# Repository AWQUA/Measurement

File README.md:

# Measurement
 This repo fully details all of AWQUA's tools for measuring water quality, with each water quality parameter in a separate subdirectory. The performance standards for these devices, and their suggested use in a water quality monitoring program, will be detailed in [Standards](https://github.com/AWQUA/Standards), and methods for communicating the data obtained through these water quality measurement tools will be described in [Communication](https://github.com/AWQUA/Communication).

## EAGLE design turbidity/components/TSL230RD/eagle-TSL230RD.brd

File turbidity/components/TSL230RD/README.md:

##AWQUA Testing documentation: TSL230RD
####**tags: turbidity, TSL230RD, light-to-frequency sensors**

##1. Component selection
Selected for turbidity detection. Mentioned in several blog posts and in two patent applications as a potentially suitable sensor for turbidity detection. Sensitive to very hight and low light levels.  
_Completed: 2014 (documentation completed 2015-07-14)_
##2. Breakout board design
**Design logic:**  
Voltage: 2.7-5.5V  
Bypass capacitor value: 100nF  
One Frequency output pin,  two sensitivity selection pins, two frequency scaling pins; output-enable pin  
[Datasheet](datasheet-TSL230RD.pdf)  
[Pinout](pinout-TSL230RD.jpg)  
[Suggested footprint](suggested-footprint-TSL230RD.jpg)  
[Eagle schematic](eagle-schematic-TSL230RD.jpg)  
[Eagle board](eagle-board-TSL230RD.jpg)  
[Test board](test-board-TSL230RD.jpg)  
[Solder mask] (solder-mask-TSL230RD.pdf)  
_Completed: 2015-07-14 (partially completed in 2014)_
##3. Board fabrication  
Check back soon -- this board is being manufactured by [OSHPark](http://oshpark.com) _as you read this_!
##4. Testing
(This component has been tested as part of a low-cost turbidimeter. For test results, see the AWQUA [`basic handheld turbidimeter`](https://github.com/AWQUA/Measurement/tree/master/turbidity/basic-handheld-turbidimeter)    
##5. Development of monitoring device  
This component has been used in an AWQUA device. Check out the [`basic handheld turbidimeter`](https://github.com/AWQUA/Measurement/tree/master/turbidity/basic-handheld-turbidimeter)!

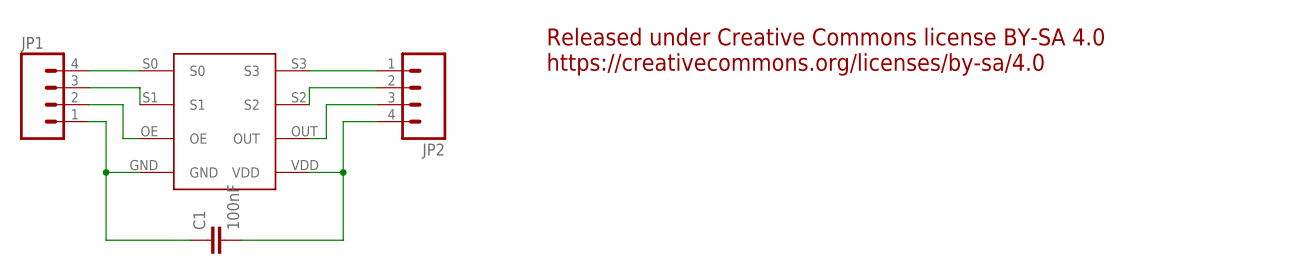
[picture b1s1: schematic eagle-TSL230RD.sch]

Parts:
C1: 100nF; 0805
JP1, JP2: M04PTH; 1X04
U$1: TSL230RDSMD; TSL230RD

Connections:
unnamed: JP1.4, U$1.S0
unnamed: JP1.3, U$1.S1
unnamed: JP1.2, U$1.OE
unnamed: C1.1, JP1.1, U$1.GND
unnamed: JP2.1, U$1.S3
unnamed: JP2.2, U$1.S2
unnamed: JP2.3, U$1.OUT
unnamed: C1.2, JP2.4, U$1.VDD

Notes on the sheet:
Released under Creative Commons license BY-SA 4.0 https://creativecommons.org/licenses/by-sa/4.0

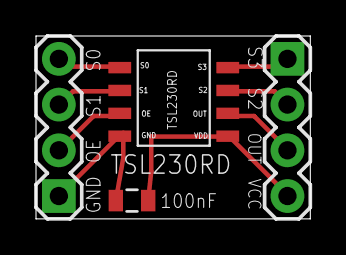
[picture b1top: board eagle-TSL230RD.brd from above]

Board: 2 copper layers, 15.2 x 10.2 mm, 4 parts (0 on the bottom side), 8 nets.

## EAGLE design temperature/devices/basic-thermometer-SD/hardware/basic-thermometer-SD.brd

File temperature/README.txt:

Contribute your designs to AWQUA! Help make water quality monitoring affordable for all citizens of Earth.

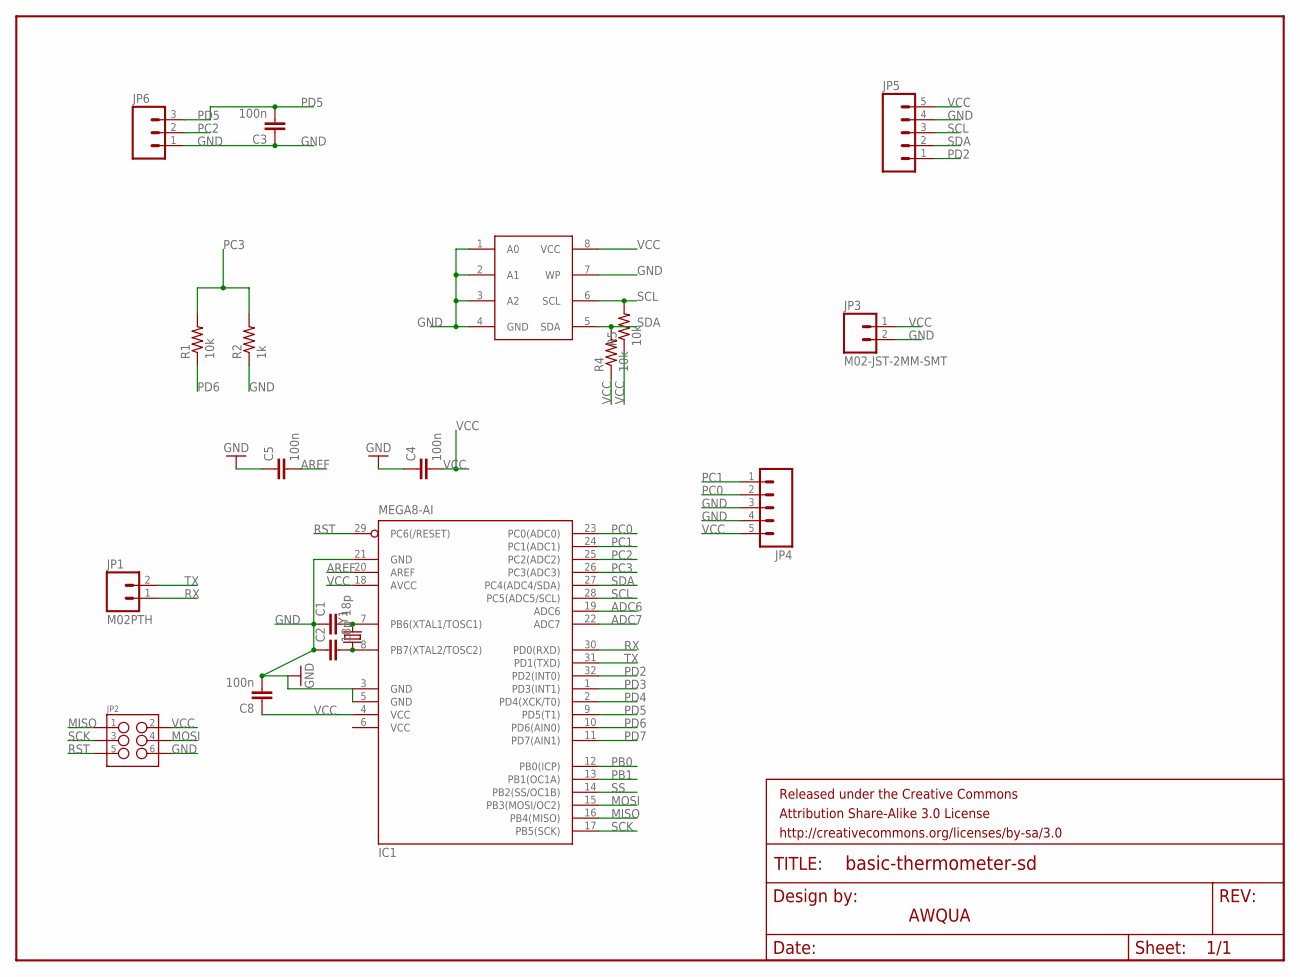
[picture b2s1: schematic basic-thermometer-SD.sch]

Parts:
C1, C2: 18p; 0603-CAP
C3, C4, C5, C8: 100n; 0603-CAP
EEPROM: AT24C256; SOIC8-LONGPAD
FRAME1: FRAME-LETTER; CREATIVE_COMMONS
IC1: MEGA8-AI; TQFP32-08
JP1: M02PTH; 1X02
JP2: M03X22X3_SILK_SM; 2X3
JP3: M02-JST-2MM-SMT; JST-2-SMD
JP4, JP5: M05PTH; 1X05
JP6: M03PTH; 1X03
R1, R4, R5: 10k; 0603-RES
R2: 1k; 0603-RES
Y1: CRYSTAL5X3; CRYSTAL-SMD-5X3

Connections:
ADC6: IC1.19 (ADC6)
ADC7: IC1.22 (ADC7)
AREF: C5.2, IC1.20 (AREF)
GND: C1.1, C2.1, C3.1, C4.1, C5.1, C8.2, EEPROM.1 (A0), EEPROM.2 (A1), EEPROM.3 (A2), EEPROM.4 (GND), EEPROM.7 (WP), IC1.3 (GND), IC1.5 (GND), IC1.21 (GND), JP2.6, JP3.2 (1), JP4.3, JP4.4, JP5.4, JP6.1, R2.1
MISO: IC1.16 (PB4(MISO)), JP2.1
MOSI: IC1.15 (PB3(MOSI/OC2)), JP2.4
PB0: IC1.12 (PB0(ICP))
PB1: IC1.13 (PB1(OC1A))
PC0: IC1.23 (PC0(ADC0)), JP4.2
PC1: IC1.24 (PC1(ADC1)), JP4.1
PC2: IC1.25 (PC2(ADC2)), JP6.2
PC3: IC1.26 (PC3(ADC3)), R1.2, R2.2
PD2: IC1.32 (PD2(INT0)), JP5.1
PD3: IC1.1 (PD3(INT1))
PD4: IC1.2 (PD4(XCK/T0))
PD5: C3.2, IC1.9 (PD5(T1)), JP6.3
PD6: IC1.10 (PD6(AIN0)), R1.1
PD7: IC1.11 (PD7(AIN1))
Q1: C2.2, IC1.8 (PB7(XTAL2/TOSC2)), Y1.1
Q2: C1.2, IC1.7 (PB6(XTAL1/TOSC1)), Y1.3 (2)
RST: IC1.29 (PC6(/RESET)), JP2.5
RX: IC1.30 (PD0(RXD)), JP1.1
SCK: IC1.17 (PB5(SCK)), JP2.3
SCL: EEPROM.6 (SCL), IC1.28 (PC5(ADC5/SCL)), JP5.3, R5.2
SDA: EEPROM.5 (SDA), IC1.27 (PC4(ADC4/SDA)), JP5.2, R4.2
SS: IC1.14 (PB2(SS/OC1B))
TX: IC1.31 (PD1(TXD)), JP1.2
VCC: C4.2, C8.1, EEPROM.8 (VCC), IC1.4 (VCC), IC1.6 (VCC), IC1.18 (AVCC), JP2.2, JP3.1 (2), JP4.5, JP5.5, R4.1, R5.1

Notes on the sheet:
AWQUA

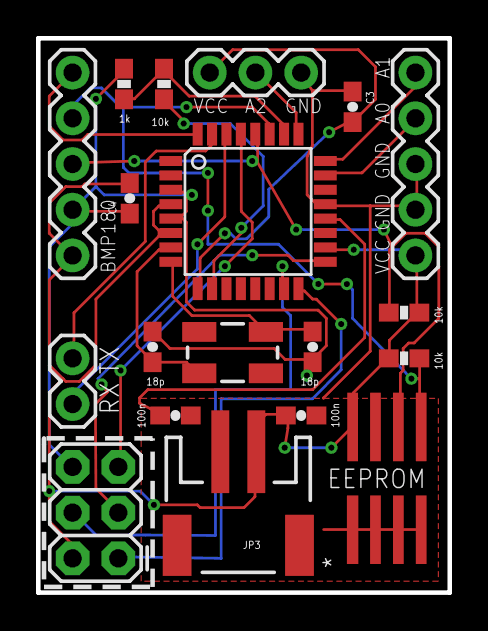
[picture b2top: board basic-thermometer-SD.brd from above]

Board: 2 copper layers, 22.9 x 30.8 mm, 21 parts (1 on the bottom side), 20 nets.

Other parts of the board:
U$1: OSHW-LOGO-S

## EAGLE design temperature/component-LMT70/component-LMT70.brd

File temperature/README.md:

# Measuring Temperature
##Why
Temperature is an important variable in the treatment of drinking water. While cheap commercial thermometers are already widely available, we aim to provide a range of thermometers that can be easily modified, outfitted with additional sensors, and paired with communications modules for telemetry of data.

##How
We have a range of tested thermometer designs. Current models are listed below, with attribute tags next to their links. Here is a quick explanation of those attribute tags:

[H] Handheld -- device is manually operated and portable  
[D] Desktop -- device is intended for stationary operation  
[B] Battery powered  
[A] Automated  
[WR] Water Resistant -- can be splashed without damaging internal electronics, but _not_ waterproof  
[I_n] Immersible -- waterproof and can withstand immersion to n meters  

* [H][B][`basic-thermometer`](basic-thermometer/) Our most basic model, which can timestamp and store 8000 temperature observations.

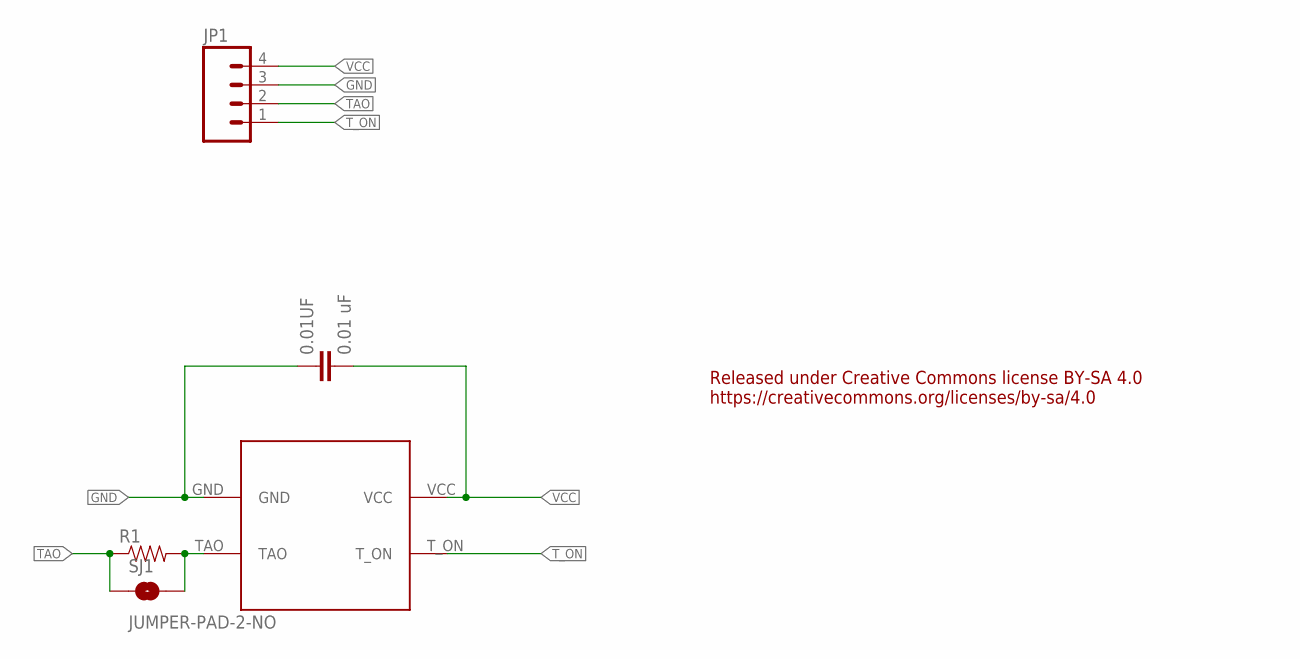
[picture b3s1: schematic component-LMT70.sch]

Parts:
0.01UF: 0.01 uF; 0603-CAP
JP1: M04NO_SILK_ALL_ROUND; 1X04_NO_SILK_ALL_ROUND
R1: RESISTOR0603-RES; 0603-RES
SJ1: JUMPER-PAD-2-NO; PAD-JUMPER-2-NO_NO_SILK
U$1: LMT70; LMT-70

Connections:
GND: 0.01UF.1, JP1.3, U$1.GND
unnamed: R1.2, SJ1.2, U$1.TAO
TAO: JP1.2, R1.1, SJ1.1
T_ON: JP1.1, U$1.T_ON
VCC: 0.01UF.2, JP1.4, U$1.VCC

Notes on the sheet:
Released under Creative Commons license BY-SA 4.0 https://creativecommons.org/licenses/by-sa/4.0

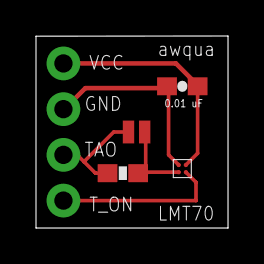
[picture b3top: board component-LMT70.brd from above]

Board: 2 copper layers, 10.7 x 10.7 mm, 5 parts (0 on the bottom side), 5 nets.

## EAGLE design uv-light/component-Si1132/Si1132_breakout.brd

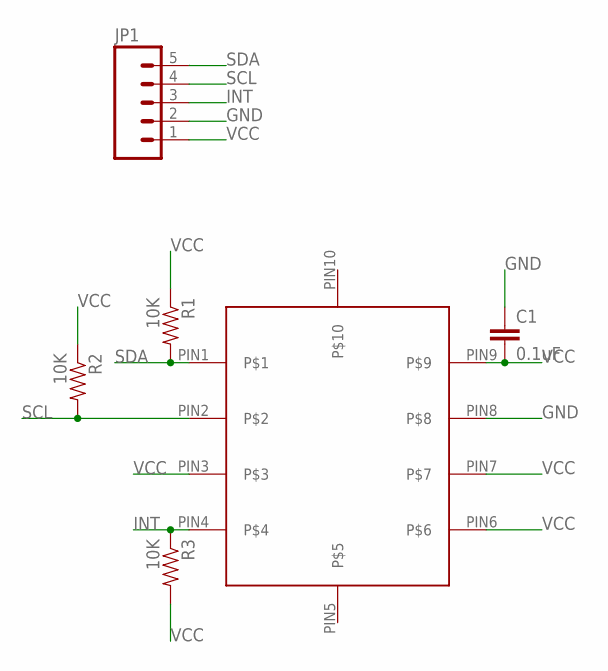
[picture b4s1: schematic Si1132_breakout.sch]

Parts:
C1: 0.1uF; 0603-CAP
JP1: M05PTH; 1X05
R1, R2, R3: 10K; 0603-RES
U$1: SI1132

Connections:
GND: C1.1, JP1.2, U$1.PIN8
INT: JP1.3, R3.1, U$1.PIN4
SCL: JP1.4, R2.2, U$1.PIN2
SDA: JP1.5, R1.2, U$1.PIN1
VCC: C1.2, JP1.1, R1.1, R2.1, R3.2, U$1.PIN3, U$1.PIN6, U$1.PIN7, U$1.PIN9

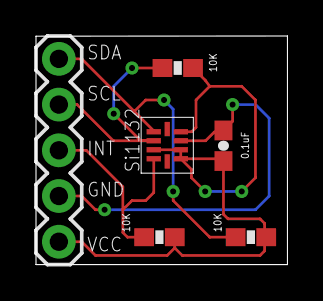
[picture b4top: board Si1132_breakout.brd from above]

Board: 2 copper layers, 14.0 x 12.7 mm, 6 parts (0 on the bottom side), 5 nets.

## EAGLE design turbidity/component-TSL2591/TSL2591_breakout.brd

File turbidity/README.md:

# Measuring Turbidity

##Why
Turbidity refers to the dirtiness or cloudiness of a water sample. Typically the majority of cloudiness in a water sample is due to suspended sediments, which can harbor pathogens and hamper the effectiveness of chemical and optical disinfection methods. Thus, while turbidity is not itself harmful, it serves as a simple real-time proxy measurement for water quality. Technicians at water treatment plants regularly measure water turbidity before and after treatment. It’s a legal requirement in many countries, and one indicator of whether treated water is safe for human consumption.

The unaided eye can distinguish cloudy water from clear water, but even visibly clear samples of water can have dangerous levels of turbidity. The standard tool for measuring turbidity (a turbidimeter) is a complex piece of equipment. Handheld units capable of analyzing a single sample vial cost several hundred dollars; automated units capable of intermittently analyzing samples from a column of flowing water can cost several thousand. An affordable, open-source solution for turbidity sampling would be a major step towards assuring the quality and sustainability of programs that seek to expand global access to treated drinking water.

##How
We have a range of tested turbidimeter designs, from barebones handheld devices to automated inline devices with dynamically updatable operating parameters and long-range data telemetry. Please note, any project name that begins with 'component' (such as ['component-TSL230RD']) is an evaluation of a sensor, not a full-fledged monitoring device.

Current models are listed below, with attribute tags next to their links. Here is a quick explanation of those attribute tags:

[H] Handheld -- device is manually operated and portable  
[D] Desktop -- device is intended for stationary operation  
[B] Battery powered  
[A] Automated  
[WR] Water Resistant -- can be splashed without damaging internal electronics, but _not_ waterproof  
[I] Immersible -- waterproof and can withstand immersion to at least one meter  

* [H][B][`basic-handheld-turbidimeter`](devices/basic-handheld-turbidimeter/) A simple, effective, lowest-cost device for manual turbidity measurments.

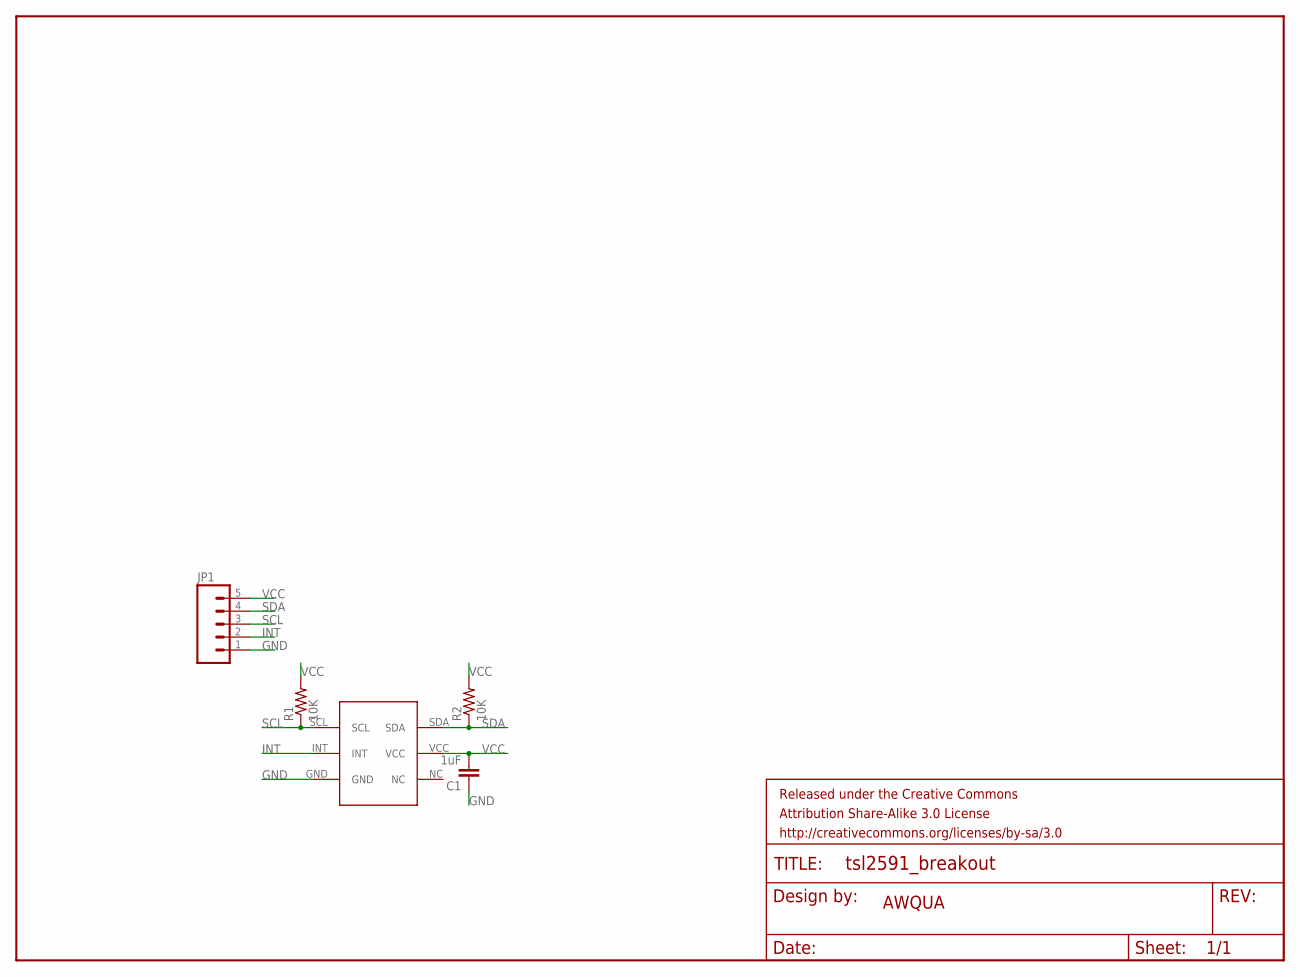
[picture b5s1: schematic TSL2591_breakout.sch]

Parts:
C1: 1uF; 0603-CAP
FRAME1: FRAME-LETTER; CREATIVE_COMMONS
JP1: M05NO_SILK; 1X05_NO_SILK
R1, R2: 10K; 0603-RES
U$1: TSL2591

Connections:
GND: C1.1, JP1.1, U$1.GND
INT: JP1.2, U$1.INT
SCL: JP1.3, R1.1, U$1.SCL
SDA: JP1.4, R2.1, U$1.SDA
VCC: C1.2, JP1.5, R1.2, R2.2, U$1.VCC

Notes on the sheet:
AWQUA

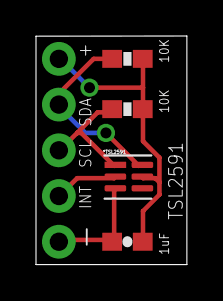
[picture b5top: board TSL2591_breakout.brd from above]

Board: 2 copper layers, 8.4 x 12.7 mm, 6 parts (0 on the bottom side), 5 nets.

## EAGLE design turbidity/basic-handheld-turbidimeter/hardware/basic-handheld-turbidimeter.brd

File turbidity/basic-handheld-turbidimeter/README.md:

#Basic Handheld Turbidimeter
##Purpose  
The Basic Handheld Turbidimeter is designed to measure turbidity on demand, portably, for the lowest possible price.  

##Function  
_How does the device measure a parameter?_  
This device is a single-beam [nephelometrer](https://en.wikipedia.org/wiki/Nephelometer). Light from an infrared light-emitting diode (IR LED) is scattered by suspended sediment as it passes through a sample of water. This scattered light is detected by an IR-sensitive [photodiode](https://en.wikipedia.org/wiki/Photodiode) mounted at a right angle to the center of the IR LED's light beam. The intensity of light detected by the photodiode is referenced to a calibration curve stored in the device's memory to interpolate the corresponding turbidity value, measured in [nephelometric turbidity units (NTU)](http://or.water.usgs.gov/grapher/fnu.html).  

_How does the device record data?_  
This device is intended for basic manual operation and does not contain storage for data.   

_How does the device display data?_  
The microcontroller at the heart of this device reads the frequency of pulses transmitted by the [photodiode unit](http://www.mouser.com/ProductDetail/ams/TSL230BRD-TR/?qs=sGAEpiMZZMu97qiQi8P%252buifvOPr%252b402N67DKHn09PFo%3d), interpolates the turbidity value from stored calibration data, and displays the turbidity value on a [four-digit display panel](http://www.electrodragon.com/product/7-segment-4-digit-display-common-anode/) (much like those used in some alarm clocks).

_What units does the device report in?_  
Like all AWQUA turbidimeters, this device reports readings in  [nephelometric turbidity units (NTU)](http://or.water.usgs.gov/grapher/fnu.html).  

_How does the device communicate data electronically?_  
This device does not possess data telemetry capabilities.  

##Use Case  
_Where can the device be safely used?_  
This device can handle temperatures up to 70C, and is intended for field conditions. It is not water proof or water resistent, however.

##Power  
_How is the device powered?_  
This device uses 3.3V DC power, and requires less than 100mA of current. A standard 3.7V lithium ion or polymer battery, or three AA alkaline batteries, would suffice to power it.

_How much power does it use?_  
In semi-automated testing, this device was capable of taking 5000 measurements on one set of three AA batteries.

##Standard and Testing  
_How was the device tested?_  
Testing procedures for this device are described in full in [An Affordable Open-Source Turbidimeter](http://www.mdpi.com/1424-8220/14/4/7142).

_How did it perform?_  
Testing results for this device are described in full in [An Affordable Open-Source Turbidimeter](http://www.mdpi.com/1424-8220/14/4/7142). The figure below shows the performance of this model of device, versus a popular commercial turbidimeter.  

_What performance standards does the device meet?_  
This device was designed and successfully tested to reliably measure turbidity values well below 1.0 NTU, which is the maximum turbidity value recommended by the World Health Organization for drinking water prior to disinfection. Please note however that this device is not certified to meet EPA requirements for the routine turbidity monitoring of treated drinking water in the United States. 

_What monitoring standards can this device be used to meet?_  
This device is one of several proven turbidimeter designs out there that can be used to meet international and World Health Organization guidelines on turbidity monitoring, yet are not able to meet the very exacting (and expensive) American and European turbidity detection standards. There is an urgent global need for simple, affordable turbidity detection, and AWQUA members are working to establish alternative turbidity detection standards to address this need. Please check out our [Standards](https://github.com/AWQUA/Standards) repository for more information.

##Construction  

###Bill of Materials
| Quantity  | Part Description | Example Price (each) |
| :-------------: | ------------- | :-------------: |
| 1 | ATMega328P-PU microprocessor  | [$2.90](http://www.electrodragon.com/product/atmega328-with-arduino-optiboot-uno/)|
| 1 | 4-digit, 7-segment display  | [$2.10](http://www.electrodragon.com/product/7-segment-4-digit-display-common-anode/)|
| 1 | 74HC595 shift register  | [$0.62](http://www.mouser.com/ProductDetail/Texas-Instruments/SN74HC595N/?qs=sGAEpiMZZMuyBeSSR239IeaeNSzgQbS%2f1btldJdqa6k%3d) |
| 1 | LMT86 temperature sensor  | [$1.00](http://www.mouser.com/ProductDetail/Texas-Instruments/LMT86LP/?qs=sGAEpiMZZMvfFCidbTccA1jyVRrxk5nB%252bTEjPRynSGM%3d)|
| 1 | TSL230BRD  | [$5.03](http://www.mouser.com/ProductDetail/ams/TSL230BRD-TR/?qs=sGAEpiMZZMu97qiQi8P%252buifvOPr%252b402N67DKHn09PFo%3d)|
| 1 | LF33ABV 3.3V Voltage regulator  | [$1.03](http://www.mouser.com/ProductDetail/STMicroelectronics/LF33ABV/?qs=sGAEpiMZZMsGz1a6aV8DcBQiArhhid1gDswAeAw%2fIB0%3d)|
| 2 | 10uF aluminum electrolytic capacitors  | [$0.24](http://www.mouser.com/ProductDetail/Nichicon/ULD1J100MDD1TD/?qs=sGAEpiMZZMvwFf0viD3Y3c1N%2fF%2fpDmX12XlNW9X9Y3vZmYyMo5GpOw%3d%3d)|
| 2 | 22pF ceramic capacitors  | [$0.03](http://www.mouser.com/ProductDetail/Vishay-BC-Components/K220J10C0GF5UH5/?qs=sGAEpiMZZMsh%252b1woXyUXj9nJp%252b8gphztXIKBUu3gv%252bs%3d)|
| 5 | 100nF ceramic capacitors  | [$0.06](http://www.mouser.com/ProductDetail/Vishay-BC-Components/K104Z15Y5VE5TL2/?qs=sGAEpiMZZMsh%252b1woXyUXj5VNmf0jXPWIrWjnp1zAXac%3d)|
| 4 | 100 ohm resistors  | [$0.10](http://www.mouser.com/ProductDetail/KOA-Speer/MOS1-2CT52R101J/?qs=sGAEpiMZZMtlubZbdhIBICYVxaT5CDYBpEIIN%2f0BoAk%3d)|
| 1 | 220 ohm resistors  | [$0.10](http://www.mouser.com/ProductDetail/KOA-Speer/MOS1-2CT52R221J/?qs=sGAEpiMZZMtlubZbdhIBICYVxaT5CDYBStqm8FrIljg%3d)|
| 1 | 1K ohm resistors 1% tolerance | [$0.10](http://www.mouser.com/ProductDetail/Vishay-Beyschlag/MBB02070C1001FCT00/?qs=sGAEpiMZZMtlubZbdhIBIAA6NYEPHyksoxlYyK2s%252btM%3d)|
| 4 | 10K ohm resistors  | [$0.10](http://www.mouser.com/ProductDetail/Vishay-Beyschlag/MBA02040C1002FCT00/?qs=sGAEpiMZZMtlubZbdhIBIP7908E9uONJr6Tgqqo7oLA%3d)|
| 1 | IR LED  | [$0.47](http://www.mouser.com/ProductDetail/Kingbright/WP7113SF4C/?qs=sGAEpiMZZMvAL21a%2fDhxMro1KOf4QOs%252bCw5JRgjZK8o%3d)|
| 1 | LED lighting driver | [$0.43](http://www.mouser.com/Search/ProductDetail.aspx?R=AL5809-30S1-7virtualkey62110000virtualkey621-AL5809-30S1-7)|
| 1 | Momentary contact button  | [$0.91](http://www.mouser.com/ProductDetail/Mountain-Switch/104-0013-EVX/?qs=sGAEpiMZZMvxtGF7dlGNpr35VnaTB25ys95hy84%252ba4o%3d)|
| 1 | SPST power switch  | [$1.15](http://www.mouser.com/ProductDetail/CHERRY/TRG22F2FBBNN/?qs=sGAEpiMZZMtNT9UGfLL4eOd3cDQgL8vM5i2VNLX9H3E%3d)|
| 100 | Header pins (0.1" spacing)  | [$.00225](http://www.electrodragon.com/product/break-away-header/)|
|||
||**Total Cost:**|**$17.70**|
###Circuit Board
####Schematic

####Layout

###Assembly
For assembly instructions, see the [Supplementary Materials](http://www.mdpi.com/1424-8220/14/4/7142/s1) for An Affordable Open-Source Turbidimeter.  
##FAQ and Troubleshooting  
###Online Resources

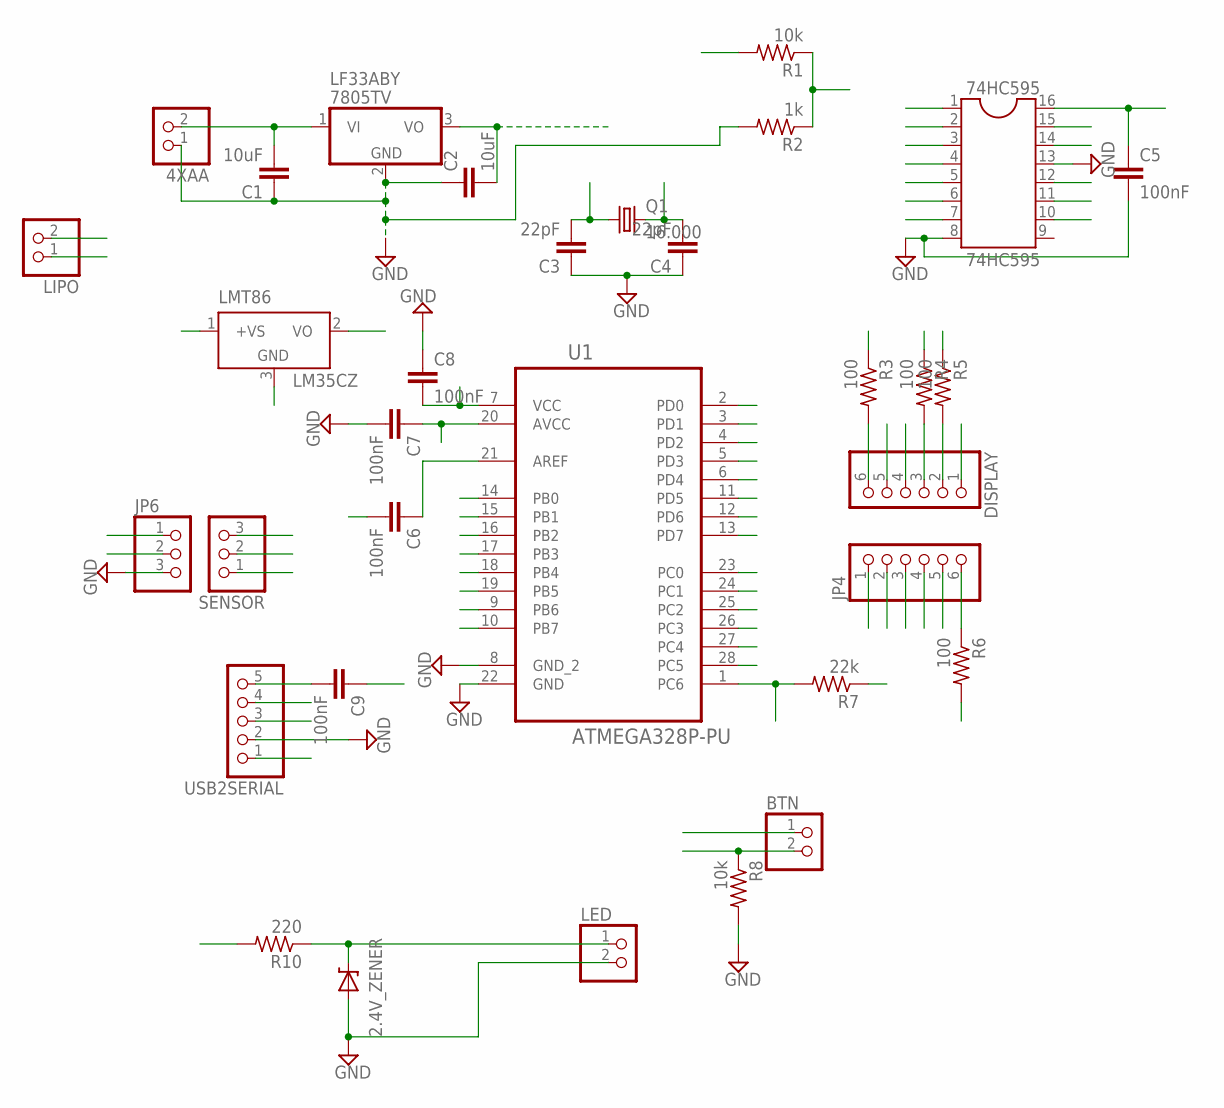
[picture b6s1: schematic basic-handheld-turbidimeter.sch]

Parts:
2.4V_ZENER: DNP; DIODE-ZENER
4XAA: PINHD-1X2; 1X02
74HC595: 74HC595; DIL16
BTN: PINHD-1X2; 1X02
C1, C2: 10uF; CAP-PTH-SMALLEZ
C3, C4: 22pF; CAP-PTH-SMALLEZ
C5, C6, C7, C8, C9: 100nF; CAP-PTH-SMALLEZ
DISPLAY: PINHD-1X6; 1X06
JP4: PINHD-1X6; 1X06
JP6: PINHD-1X3; 1X03
LED: PINHD-1X2; 1X02
LF33ABY: 7805TV; TO220V
LIPO: PINHD-1X2; 1X02
LMT86: LM35CZ; TO92
Q1: 16.000; HC49/S
R1, R8: 10k; 0207/12
R2: 1k; 0207/12
R3, R4, R5, R6: 100; 0207/12
R7: 22k; 0207/12
R10: 220; 0207/12
SENSOR: PINHD-1X3; 1X03
U1: ATMEGA328P-PU; DIP254P762X457-28
USB2SERIAL: PINHD-1X5; 1X05

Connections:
3V3: 74HC595.10, 74HC595.16, BTN.1, C2.2, C5.1, C7.1, C8.2, LF33ABY.3 (VO), LIPO.2, LMT86.1 (+VS), R1.2, R7.1, SENSOR.1, U1.7 (VCC), U1.20 (AVCC), USB2SERIAL.1
595A: 74HC595.15, DISPLAY.5
595B: 74HC595.1, DISPLAY.1
595C: 74HC595.2, JP4.4
595D: 74HC595.3, JP4.2
595E: 74HC595.4, JP4.1
595F: 74HC595.5, DISPLAY.4
595G: 74HC595.6, JP4.5
595H: 74HC595.7, JP4.3
GND: 2.4V_ZENER.P$2 (A), 4XAA.1, 74HC595.8, 74HC595.13, C1.1, C2.1, C3.1, C4.1, C5.2, C6.2, C7.2, C8.1, JP6.3, LED.2, LF33ABY.2 (GND), LIPO.1, LMT86.3 (GND), R2.2, R8.2, U1.5 (PD3), U1.8 (GND_2), U1.13 (PD7), U1.22 (GND), USB2SERIAL.2
LED: 2.4V_ZENER.P$1 (C), LED.1, R10.1
unnamed: 4XAA.2, C1.2, LF33ABY.1 (VI)
unnamed: C6.1, U1.21 (AREF)
unnamed: C9.2, USB2SERIAL.5
unnamed: DISPLAY.6, R3.2
unnamed: DISPLAY.3, R4.2
unnamed: DISPLAY.2, R5.2
unnamed: JP4.6, R6.1
PB0: 74HC595.11, U1.14 (PB0)
PB1: SENSOR.3, U1.15 (PB1)
PB2: R6.2, U1.16 (PB2)
PB3: JP6.1, U1.17 (PB3)
PB4: JP6.2, U1.18 (PB4)
PB5: SENSOR.2, U1.19 (PB5)
PB6: C3.2, Q1.1, U1.9 (PB6)
PB7: C4.2, Q1.2, U1.10 (PB7)
PC0: LMT86.2 (VO), U1.23 (PC0)
PC1: R5.1, U1.24 (PC1)
PC2: R4.1, U1.25 (PC2)
PC3: R3.1, U1.26 (PC3)
PC4: R1.1, R2.1, U1.27 (PC4)
PC5: U1.28 (PC5)
PC6: C9.1, R7.2, U1.1 (PC6)
PD0: U1.2 (PD0), USB2SERIAL.3
PD1: U1.3 (PD1), USB2SERIAL.4
PD2: BTN.2, R8.1, U1.4 (PD2)
PD4: R10.2, U1.6 (PD4)
PD5: 74HC595.14, U1.11 (PD5)
PD6: 74HC595.12, U1.12 (PD6)

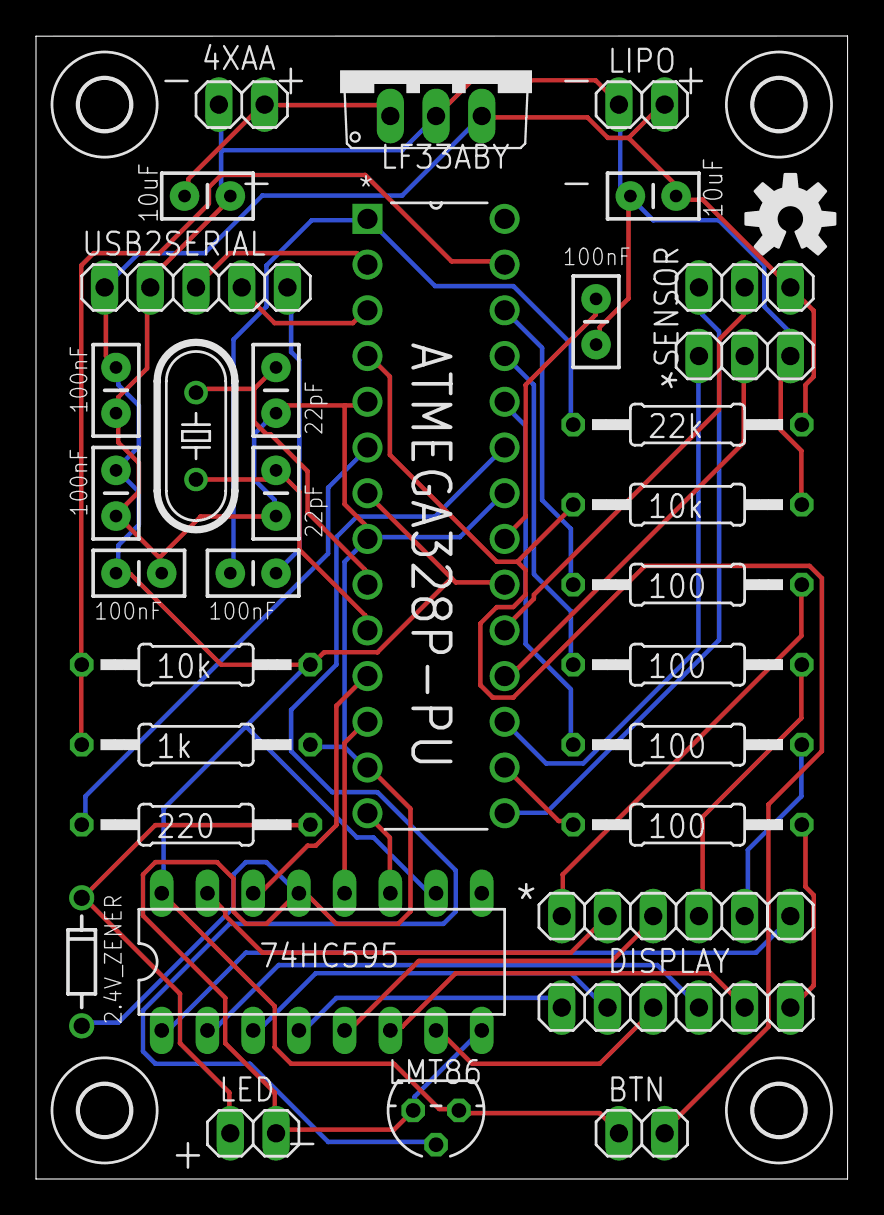
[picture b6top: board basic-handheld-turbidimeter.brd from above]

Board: 2 copper layers, 45.1 x 63.5 mm, 38 parts (0 on the bottom side), 38 nets.

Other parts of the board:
U$1, U$2, U$3, U$4: 2,8
U$5: OSHW-LOGO-M

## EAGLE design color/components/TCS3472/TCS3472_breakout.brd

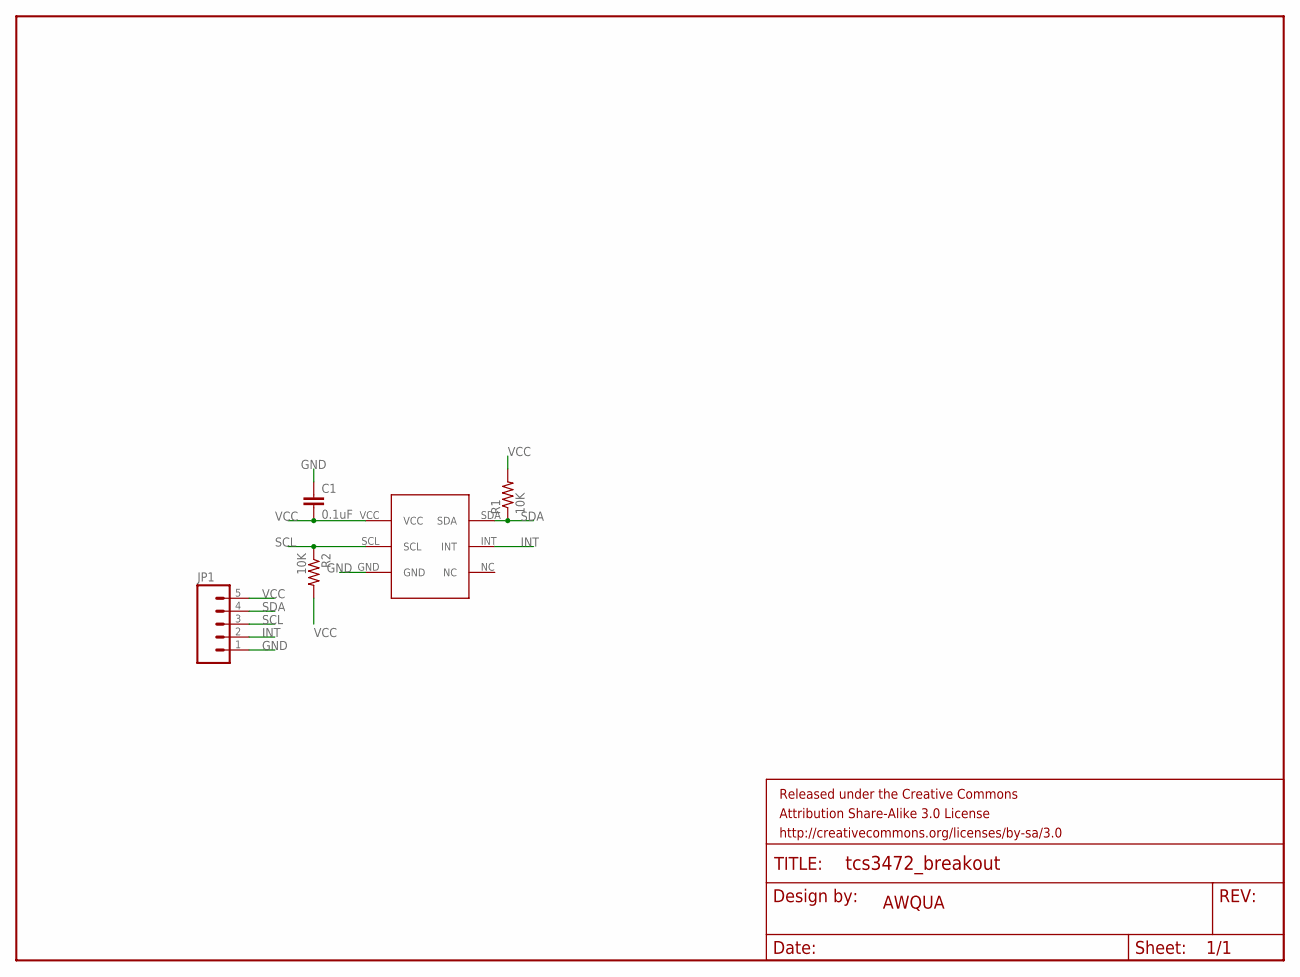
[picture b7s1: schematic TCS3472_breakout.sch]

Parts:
C1: 0.1uF; 0603-CAP
FRAME1: FRAME-LETTER; CREATIVE_COMMONS
JP1: M05NO_SILK; 1X05_NO_SILK
R1, R2: 10K; 0603-RES
U$2: TCS3472

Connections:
GND: C1.1, JP1.1, U$2.GND
INT: JP1.2, U$2.INT
SCL: JP1.3, R2.1, U$2.SCL
SDA: JP1.4, R1.1, U$2.SDA
VCC: C1.2, JP1.5, R1.2, R2.2, U$2.VCC

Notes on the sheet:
AWQUA

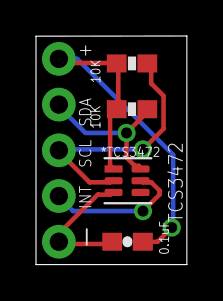
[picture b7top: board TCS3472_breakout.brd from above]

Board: 2 copper layers, 8.4 x 12.7 mm, 6 parts (0 on the bottom side), 5 nets.

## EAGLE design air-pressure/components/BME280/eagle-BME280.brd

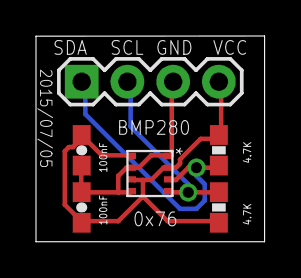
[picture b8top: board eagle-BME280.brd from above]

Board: 2 copper layers, 12.7 x 11.4 mm, 6 parts (0 on the bottom side), 4 nets.

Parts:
C1, C2: 100nF; 0603-CAP
JP1: 1X04
R1, R2: 4.7K; 0603-RES
U$1: BMP280

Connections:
GND: C1.2, C2.2, JP1.3, U$1.PIN1, U$1.PIN5, U$1.PIN7
SCL: JP1.2, R2.2, U$1.PIN4
SDA: JP1.1, R1.2, U$1.PIN3
VCC: C1.1, C2.1, JP1.4, R1.1, R2.1, U$1.PIN2, U$1.PIN6, U$1.PIN8

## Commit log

2015-06-22 editing readme, updating file structure
2015-06-22 editing links in readme
2015-06-22 relative readme links
2015-06-22 Updating readme, adding license
2015-06-29 Initial push
    Moving folder structure and basic set of files from sandbox
2015-07-06 adding air-pressure and relative-humidity parameter directories
2015-07-08 added OSHW logo to main board, added seven segment helper board
2015-07-11 adding component boards for a few parameters
2015-07-14 adding component-TSL230RD to turbidity folder
2015-07-14 updating caseware and software folders
2015-07-15 added sensor board, testing documentation
2015-07-15 added current regulator for IR LED
2015-07-16 adding basic inline turbidimeter, main board
2015-07-27 adding new components
2015-08-06 Updating BOM for basic handheld turbidimeter
2015-09-06 adding sensor APDS-9960 to gesture folder
2015-09-06 updating TSL2591 files
2015-09-06 adding LMT70 temperature sensor
2015-09-06 added folder for smartphone turbidimeter project
2015-09-08 update to basic-thermometer-SD
2015-09-22 moving components into subfolders
2015-10-05 updating BOM prices for basic handheld turbidimeter
2015-10-13 updating pdfs of board and schematic
2015-10-29 updates to inline turbidimeter, including test data
2016-03-25 Improved Multi Sensor Board Schematic
    All nets were visibly labeled to allow for easy readability. PDF was
    also updated with the new schematic.
2016-03-27 removed empty project directory
2016-03-27 refactored devices directory into individual repos
2016-03-27 adding publications section
2016-03-28 moving breakout boards to separate repos
2016-03-28 moving parameters into one folder
2016-03-28 removed wiki link

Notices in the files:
parts and their libraries:
SparkFun-Resistors: Licensing: Creative Commons ShareAlike 4.0 International - https://creativecommons.org/licenses/by-sa/4.0
SparkFun-Connectors: Licensing: CC v3.0 Share-Alike You are welcome to use this library for commercial purposes.
SparkFun-Aesthetics: Released under the Creative Commons
